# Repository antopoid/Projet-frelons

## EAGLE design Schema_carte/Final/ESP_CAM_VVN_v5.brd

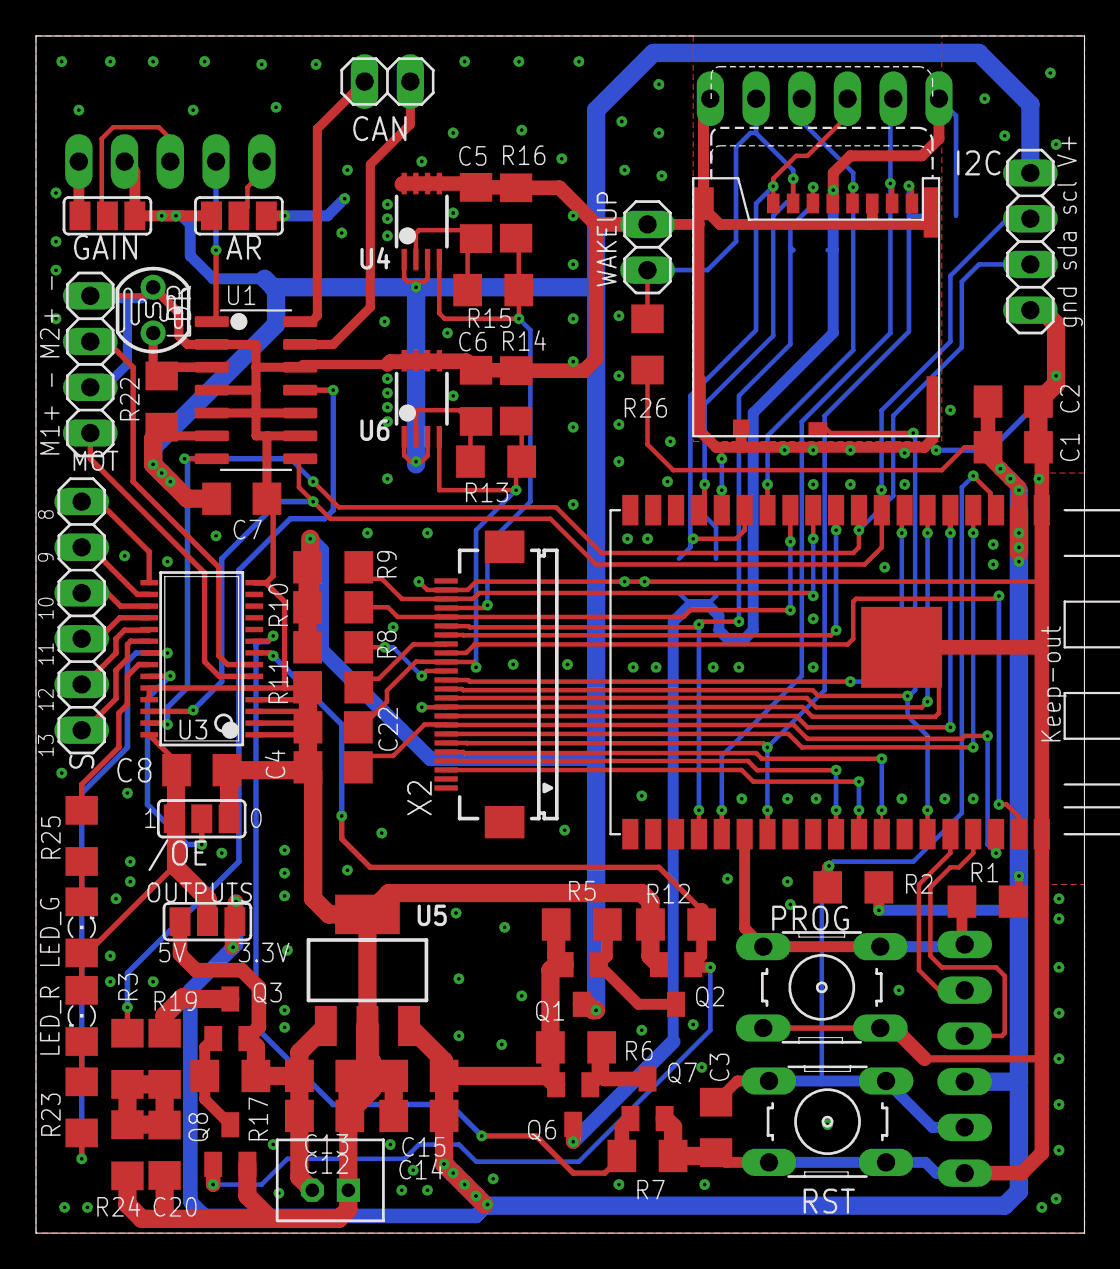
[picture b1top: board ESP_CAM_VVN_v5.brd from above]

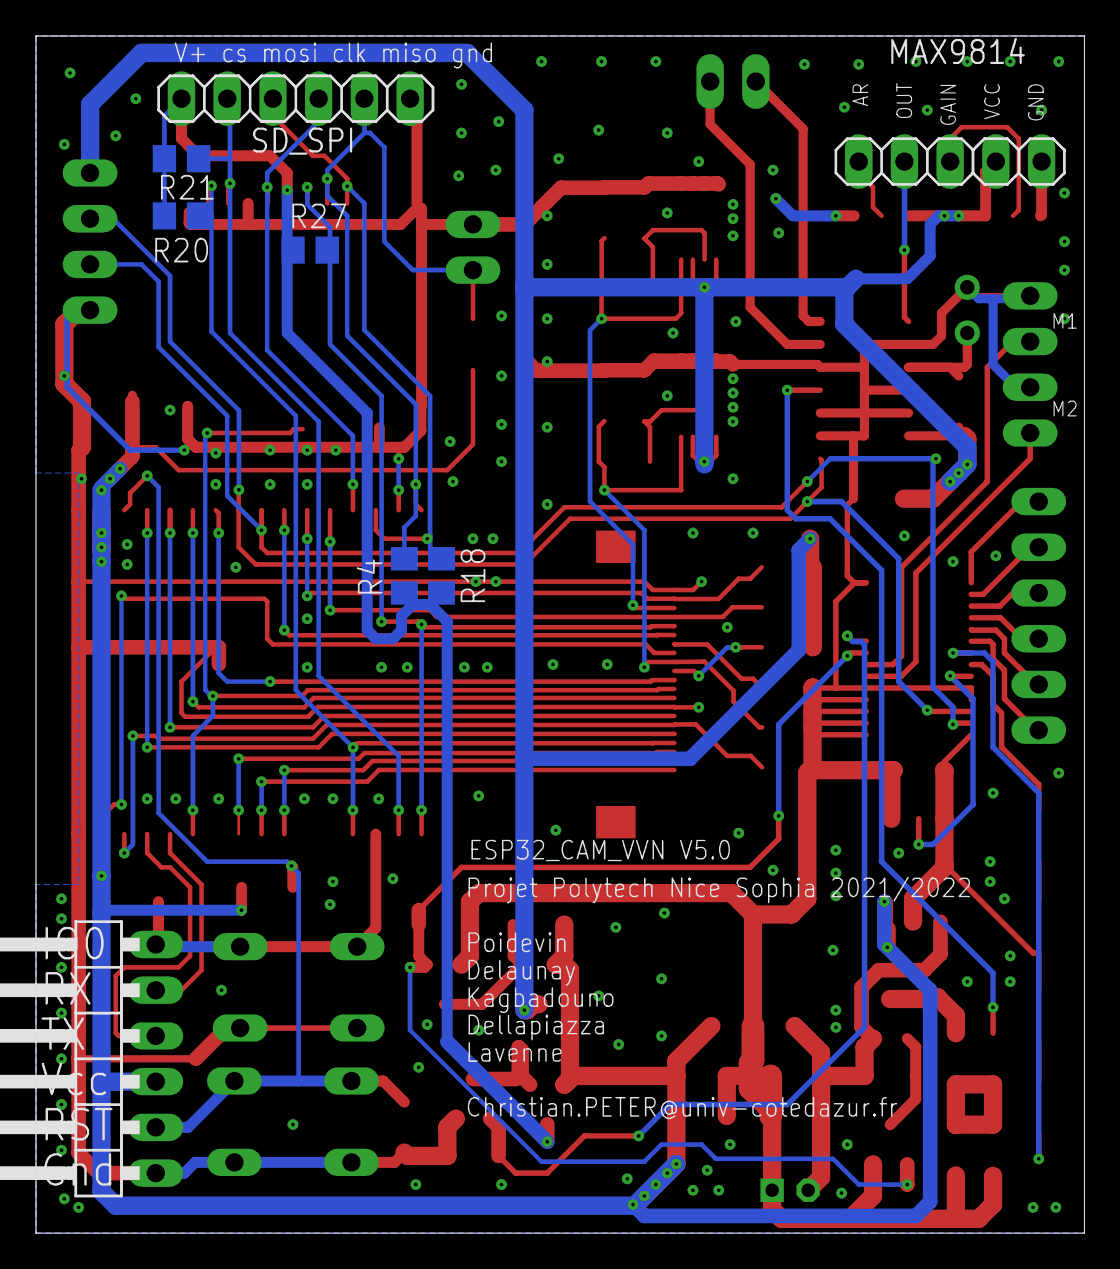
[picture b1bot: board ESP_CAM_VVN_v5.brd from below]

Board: 2 copper layers, 58.2 x 66.5 mm, 73 parts (8 on the bottom side), 64 nets.

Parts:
/OE: SJ_2
AR: SJ_2
C1, C3, C7, C8, C13, C15, C20, C22: 100n; C1206
C2, C12, C14: 10u; C1206
C4: 15p; C1206
C5, C6: 1u; C1206
CAN: 1X02
GAIN: SJ_2
I2C: 1X04
JP6: 1X06/90
LDR: VT93N2; VT900
LED_G: 1206
LED_R: 1206
MAX9814: 1X05
MOT: 1X04
OUTPUTS: SJ_2
PROG: B3F-10XX
Q1, Q3, Q6: SI2305CDS; SOT23
Q2, Q7, Q8: BSS131; SOT23
R1, R13, R26: 100k; R1206
R2, R11, R16, R22, R24: 10k; R1206
R3, R8: 0; R1206
R4, R18, R20, R21, R27: 47k; R0805
R5, R6, R7, R12, R17: 33k; R1206
R9, R10: 4.7K; R1206
R14: 220k; R1206
R15: 12k; R1206
R19: 150k; R1206
R23: 150; R1206
R25: 100; R1206
RST: B3F-10XX
S: 1X06
SD1: MICRO-SD-8; MICROSDMOLEX
SD_SPI: 1X06
U1: MCP3428-E/SL; SOIC127P600X175-14N
U2: ESP32-WROVER-E; ESP32-WROVER
U3: PCA9685PW; TSSOP28
U4, U6: MIC5239-ADJMM; MSOP08
U5: MIC5239S; SOT223
WAKEUP: 1X02
X1: B2B-PH-K-S
X2: FH12-24S-0.5SH

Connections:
5V_MES: R3.1, U1.11
+5V: C12.1, C13.1, OUTPUTS.1, Q3.2, R17.2, U5.1, X1.2
+5V/1: Q3.3, R19.1
AR: AR.2, MAX9814.1
CA_D0_SD_D1: R20.2, SD1.P$1, U2.IO4, X2.6
CA_D1: U2.IO5, X2.4
CA_D2: U2.IO18, X2.3
CA_D3: U2.IO19, X2.5
CA_D4: U2.SENSOR_VP, X2.7
CA_D5: U2.SENSOR_VN, X2.9
CA_D6: U2.IO34, X2.11
CA_D7: U2.IO35, X2.13
CA_HREF: U2.IO23, X2.16
CA_PCLK: C4.2, U2.IO22, X2.8
CA_PWDN: R11.2, X2.17
CA_PWDN_SD_CLK: SD1.P$4, SD_SPI.4, U2.IO14
CA_RST_SD_CMD: R27.2, SD1.P$6, U2.IO15, X2.19
CA_SIO_C: R10.2, U2.IO27, X2.20
CA_SIO_D: R9.2, U2.IO26, X2.22
CA_VSYNC: U2.IO25, X2.18
CA_XCLK_SD_DET: SD1.P$14, U2.IO21, X2.12
GAIN: GAIN.2, MAX9814.3
GND: /OE.1, AR.3, C1.2, C2.2, C3.2, C4.1, C5.2, C6.2, C7.2, C8.2, C12.2, C13.2, C14.2, C15.2, C20.2, C22.2, GAIN.1, I2C.4, JP6.1, LDR.1, MAX9814.5, MOT.2, MOT.4, PROG.3, PROG.4, Q2.2, Q7.2, Q8.2, R7.2, R11.1, R12.2, R14.1, R16.1, R24.2, RST.3, RST.4, SD1.P$3, SD1.P$9, SD1.P$10, SD1.P$11, SD1.P$12, SD1.P$13, SD_SPI.6, U1.2, U1.4, U1.5, U1.9, U1.10, U1.12, U2.GND, U2.GND1, U2.GND2, U2.GND3, U3.1, U3.2, U3.3, U3.4, U3.5, U3.14, U3.24, U3.25, U4.5, U4.6, U4.7, U4.8, U5.2, U5.4, U6.5, U6.6, U6.7, U6.8, WAKEUP.1, X1.1, X2.10, X2.23
IO0: JP6.6, PROG.1, PROG.2, R1.2, U2.IO0
LDR: LDR.2, R22.2, U1.3
LED_G: R25.1, U3.22
LED_R: R23.1, U3.21
M1: MOT.1, U3.6
M2: MOT.3, U3.7
unnamed: Q1.1, Q2.3, R5.1
unnamed: MAX9814.2, U1.1
unnamed: C20.1, R3.2, R19.2, R24.1
unnamed: /OE.3, C8.1, LED_G.A, LED_R.A, OUTPUTS.2, U3.28
unnamed: CAN.2, U1.13
unnamed: Q6.1, Q7.3, R6.1
unnamed: LED_R.C, R23.2
unnamed: LED_G.C, R25.2
unnamed: Q3.1, Q8.3, R17.1
unnamed: R8.2, X2.14
unnamed: CAN.1, U1.14
unnamed: S.1, U3.15
unnamed: S.2, U3.16
unnamed: S.3, U3.17
unnamed: S.4, U3.18
unnamed: S.5, U3.19
unnamed: S.6, U3.20
unnamed: R13.1, R14.2, U6.2
unnamed: R15.1, R16.2, U4.2
OE: /OE.2, U3.23
POWER: Q2.1, Q8.1, R12.1, U3.8
POWER_SD: Q7.1, R7.1, U3.9
RST: C3.1, JP6.2, R2.1, RST.1, RST.2, U2.EN
RX: JP6.5, U2.RXD0
SCL: I2C.2, U1.8, U2.IO32, U3.26
SDA: I2C.3, U1.7, U2.IO33, U3.27
SD_D0: R21.2, SD1.P$2, SD_SPI.2, U2.IO2
SD_D2: R18.2, SD1.P$8, SD_SPI.3, U2.IO12
SD_D3: R4.2, R26.2, SD1.P$7, SD_SPI.5, U2.IO13, WAKEUP.2
TX: JP6.4, U2.TXD0
V1_2.7V: C5.1, R15.2, U4.4, X2.21
V2_1.8V: C6.1, C22.1, R13.2, U6.4, X2.15
V+: AR.1, C7.1, GAIN.3, I2C.1, MAX9814.4, Q1.3, R8.1, R9.1, R10.1, R22.1, U1.6, U4.1, U4.3, U6.1, U6.3
V+_SD: Q6.3, R4.1, R18.1, R20.1, R21.1, R27.1, SD1.P$5, SD_SPI.1
VCC: C1.1, C2.1, C14.1, C15.1, JP6.3, OUTPUTS.3, Q1.2, Q6.2, R1.1, R2.2, R5.2, R6.2, R26.1, U2.VDD33, U5.3

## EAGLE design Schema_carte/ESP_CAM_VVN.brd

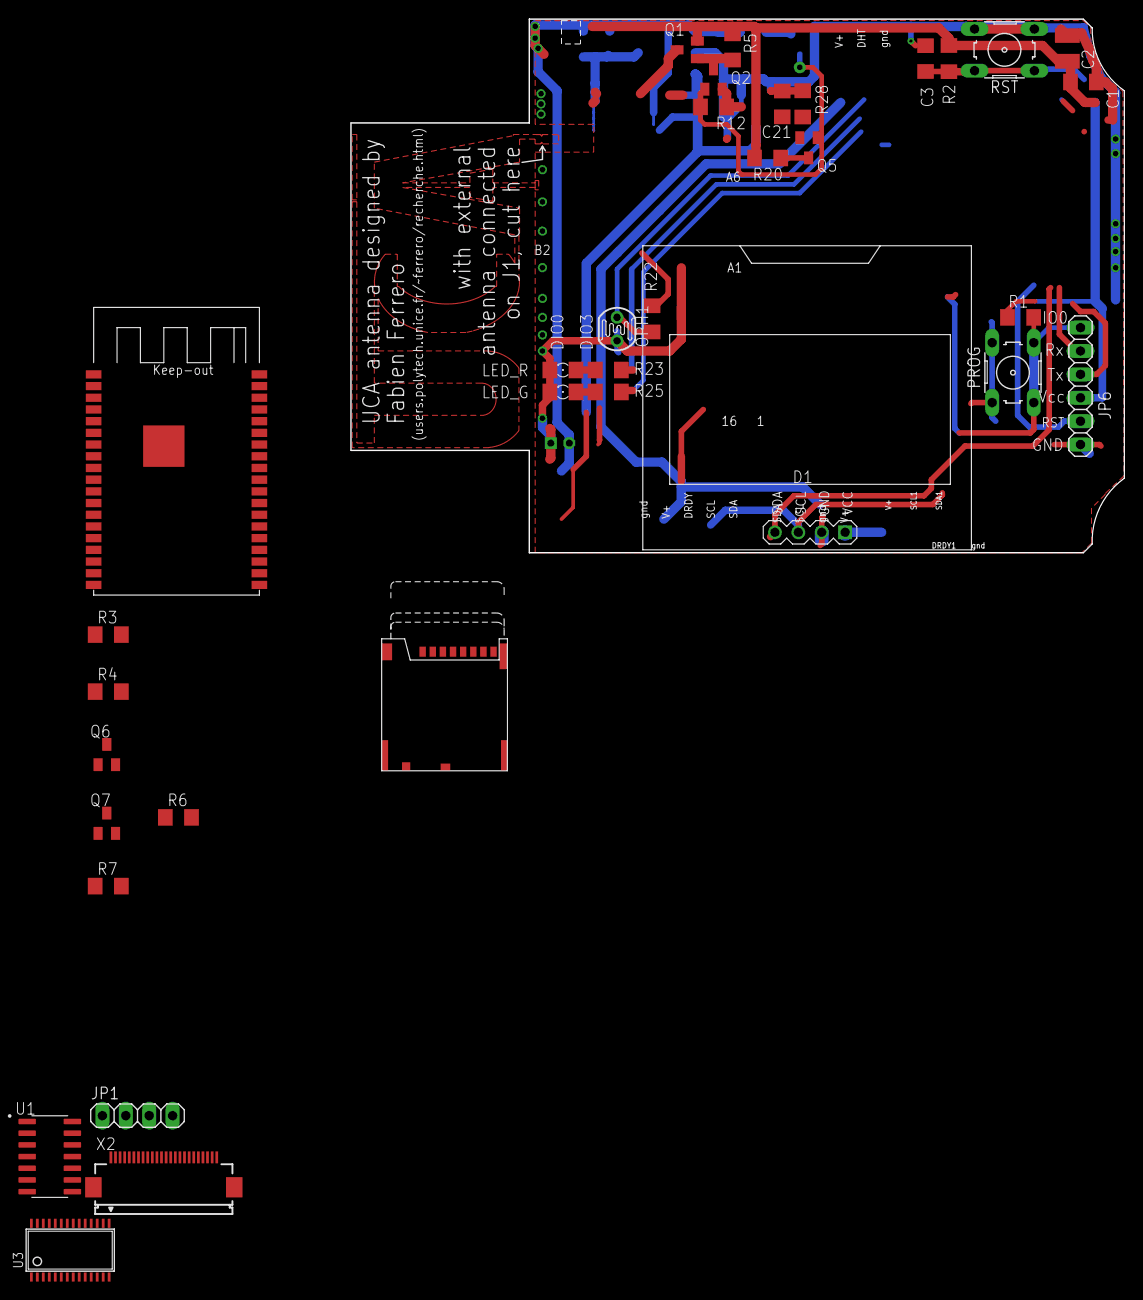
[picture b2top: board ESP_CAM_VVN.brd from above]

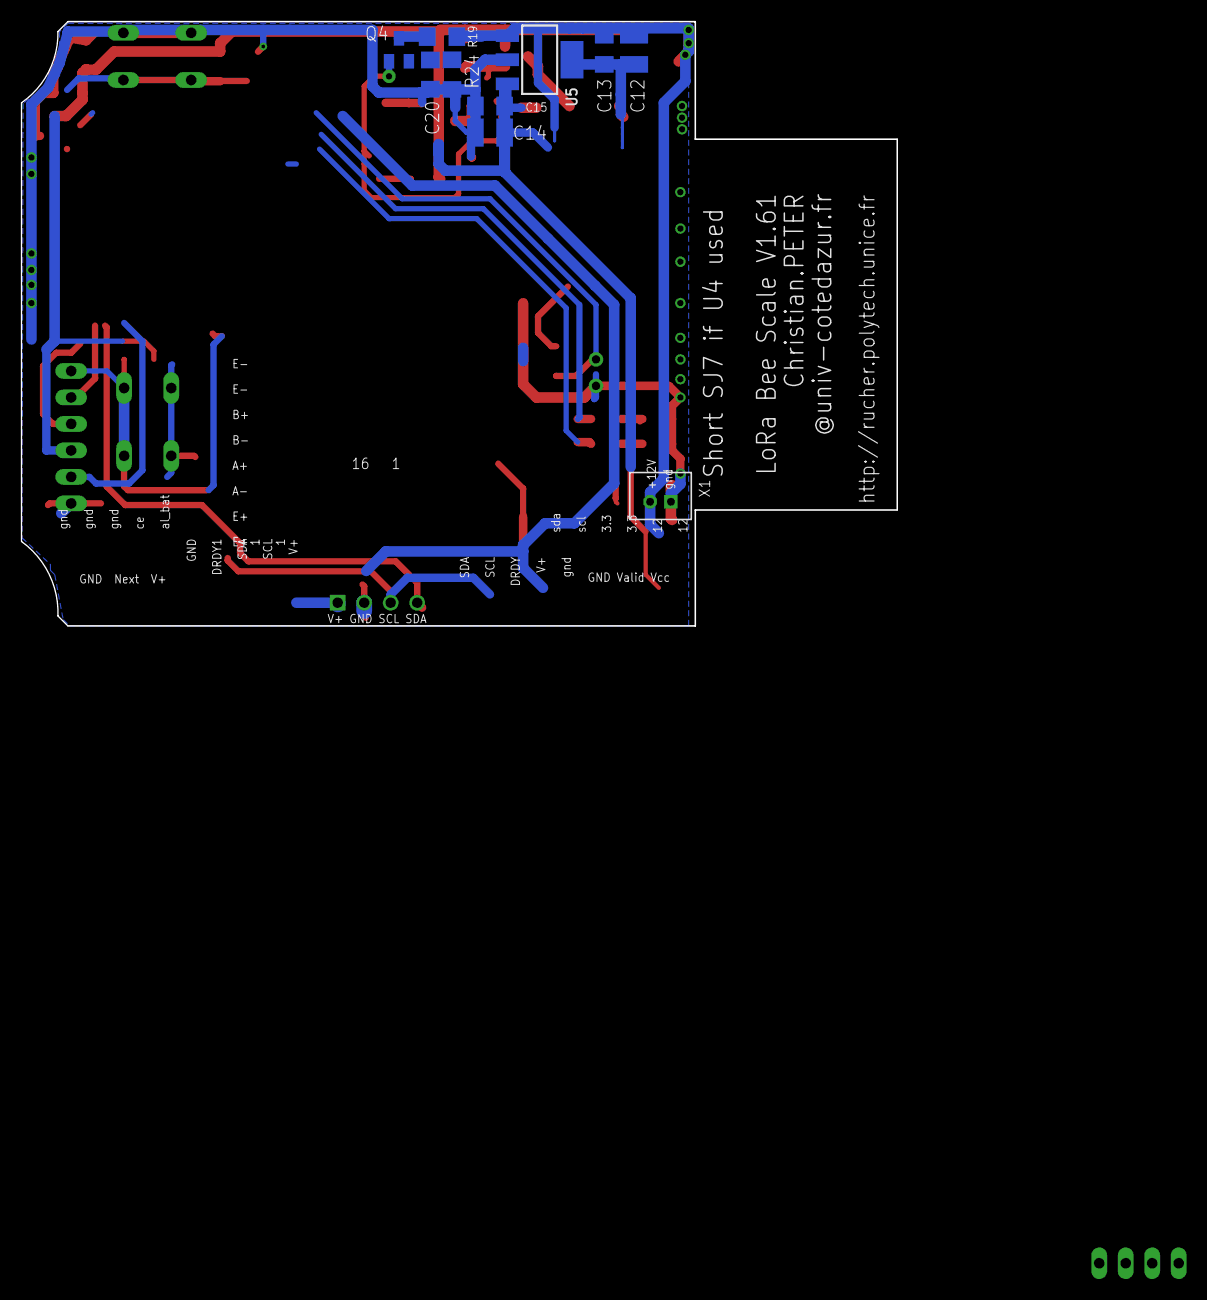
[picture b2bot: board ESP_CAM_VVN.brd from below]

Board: 2 copper layers, 84.0 x 57.9 mm, 45 parts (10 on the bottom side), 28 nets.

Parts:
C1, C3, C13, C15, C20, C21: 100n; C1206
C2, C12, C14: 10u; C1210
D1: DISPLAY-OLED-128X64-I2C1.3_BIS; DISPLAY-OLED-128X64-1.3-I2C_BIS
JP1: 1X04
JP6: 1X06
LED_G: 1206
LED_R: 1206
OPH1: VT93N2; VT900
PROG: B3F-10XX
Q1, Q6: SI2305CDS; SOT23
Q2, Q7: BSS131; SOT23
Q4, Q5: BSS138; SOT23
R1: 100k; R1206
R2, R22, R24, R28: 10k; R1206
R3, R4: 0; R1206
R5, R6, R7, R12: 33k; R1206
R19: 150k; R1206
R20: 27k; R1206
R23: 150; R1206
R25: 100; R1206
RST: B3F-10XX
SD1: MICRO-SD-8; MICROSDMOLEX
U1: MCP3428-E/SL; SOIC127P600X175-14N
U2: ESP32-WROVER-E; ESP32-WROVER
U3: PCA9685PW; TSSOP28
U5: MIC5239S; SOT223
X1: B2B-PH-K-S
X2: FH12-24S-0.5SH

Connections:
+12V: C12.1, C13.1, R19.1, U5.1, X1.2
CA_D0_SD_D1: SD1.P$8, U2.IO4
CA_XCLK_SD_DET: SD1.P$14, U2.IO21
GND: C1.2, C2.2, C3.2, C12.2, C13.2, C14.2, C15.2, C20.2, C21.2, D1.2, JP1.4, JP6.1, LED_G.C, LED_R.C, OPH1.1, PROG.3, PROG.4, Q2.2, Q7.2, R7.2, R12.2, R24.2, R28.2, RST.3, RST.4, SD1.P$6, SD1.P$9, SD1.P$10, SD1.P$11, SD1.P$12, SD1.P$13, U2.GND, U2.GND1, U2.GND2, U2.GND3, U3.14, U5.2, U5.4, X1.1
IO0: JP6.6, PROG.1, PROG.2, R1.2
LDR: OPH1.2, R22.2
unnamed: Q1.1, Q2.3, R5.1
unnamed: Q4.3, R19.2
unnamed: C20.1, Q4.2, R3.2, R24.1
unnamed: C21.1, Q5.2, R4.2, R28.1
unnamed: Q5.3, R20.1
unnamed: Q6.1, Q7.3, R6.1
unnamed: LED_R.A, R23.2
unnamed: LED_G.A, R25.2
POWER: Q2.1, Q4.1, Q5.1, R12.1
POWER_SD: Q7.1, R7.1
RST: C3.1, JP6.2, R2.1, RST.1, RST.2, U2.EN
RX: JP6.5, U2.RXD0
SCL: D1.3, JP1.2, U1.8, U2.IO32
SDA: D1.4, JP1.3, U1.7, U2.IO33, U3.27
SD_CLK: SD1.P$5, U2.IO14
SD_D0: SD1.P$7, U2.IO2
SD_D2: SD1.P$1, U2.IO12
SD_D3: SD1.P$2, U2.IO13
TX: JP6.4, U2.TXD0
V+: D1.1, JP1.1, Q1.3, R22.1, U1.6, U3.28
V+_SD: Q6.3, SD1.P$4
VCC: C1.1, C2.1, C14.1, C15.1, JP6.3, Q1.2, Q6.2, R1.1, R2.2, R5.2, R6.2, R20.2, U2.VDD33, U5.3

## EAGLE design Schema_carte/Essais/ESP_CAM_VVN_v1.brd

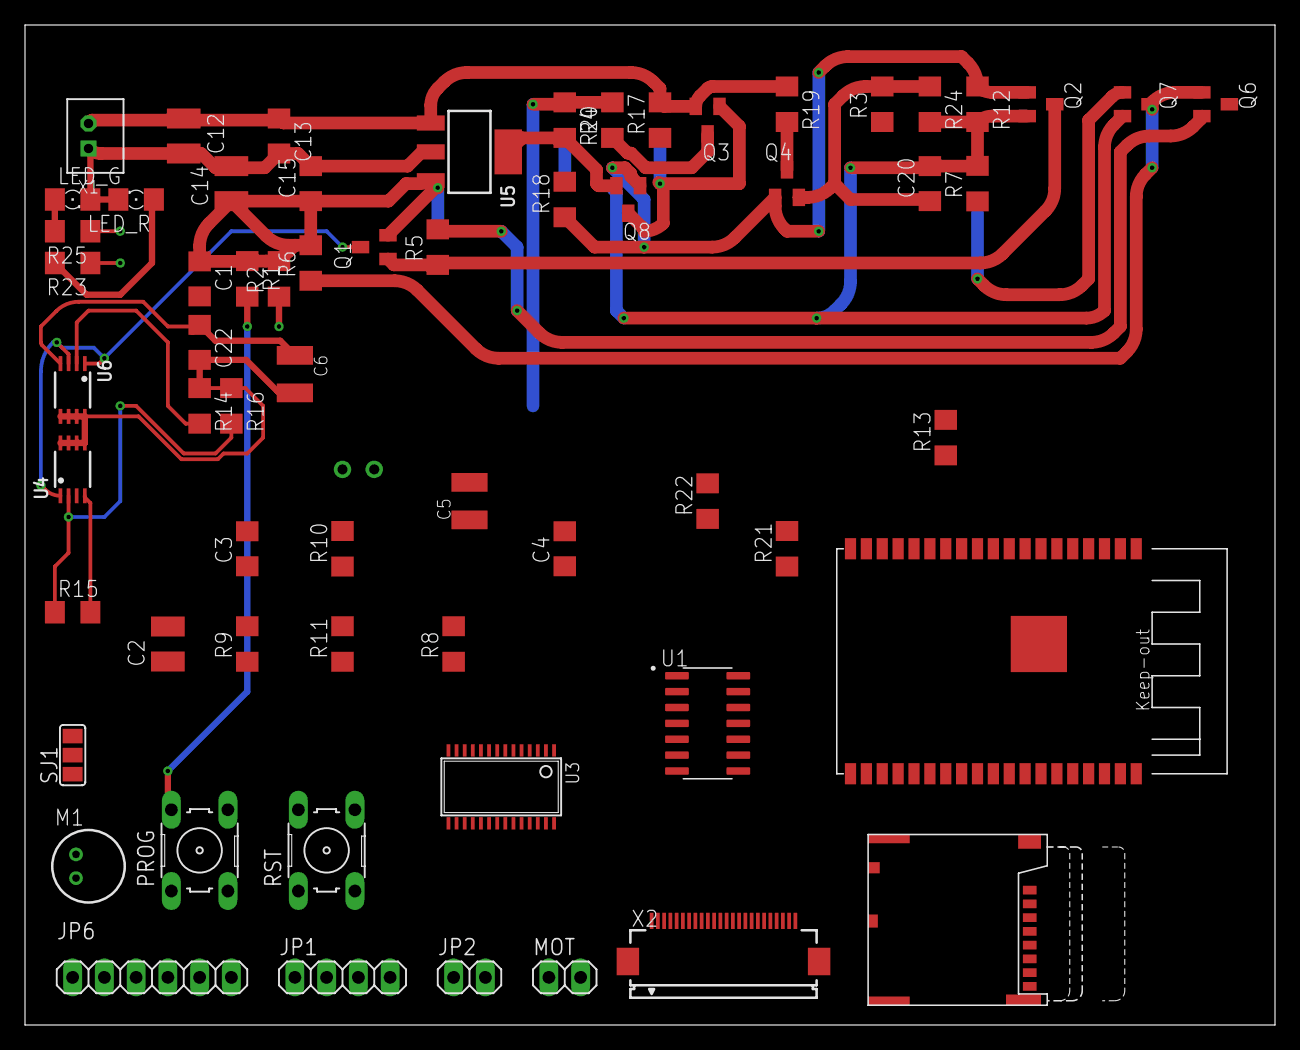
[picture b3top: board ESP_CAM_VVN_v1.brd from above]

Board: 2 copper layers, 100.0 x 80.0 mm, 64 parts (1 on the bottom side), 56 nets.

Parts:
C1, C3, C13, C15, C20, C22: 100n; C1206
C2, C12, C14: 10u; C1210
C4: 15p; C1206
C5, C6: 1u; C1210K
JP1: 1X04
JP2: 1X02
JP6: 1X06
LED_G: 1206
LED_R: 1206
M1: ELECTRET_MICROPHON-WM-62PC/62PK; WM-62PC/62PK
MOT: 1X02
OPH1: VT93N2; VT900
PROG: B3F-10XX
Q1, Q3, Q6: SI2305CDS; SOT23
Q2, Q7, Q8: BSS131; SOT23
Q4: BSS138; SOT23
R1, R13: 100k; R1206
R2, R11, R16, R21, R22, R24: 10k; R1206
R3, R8: 0; R1206
R4, R5, R6, R7, R12, R17, R18, R20: 33k; R1206
R9, R10: 4.7K; R1206
R14: 220k; R1206
R15: 12k; R1206
R19: 150k; R1206
R23: 150; R1206
R25: 100; R1206
RST: B3F-10XX
SD1: MICRO-SD-8; MICROSDMOLEX
SJ1: SJ_2
U1: MCP3428-E/SL; SOIC127P600X175-14N
U2: ESP32-WROVER-E; ESP32-WROVER
U3: PCA9685PW; TSSOP28
U4, U6: MIC5239-ADJMM; MSOP08
U5: MIC5239S; SOT223
X1: B2B-PH-K-S
X2: FH12-24S-0.5SH

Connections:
5V_MES: R4.2, R20.1, U1.11
+5V: C12.1, C13.1, Q3.2, R17.2, R19.1, U5.1, X1.2
+5V/1: Q3.3, R4.1, SJ1.1
CA_D0_SD_D1: SD1.P$8, U2.IO4, X2.19
CA_D1: U2.IO5, X2.21
CA_D2: U2.IO18, X2.22
CA_D3: U2.IO19, X2.20
CA_D4: U2.SENSOR_VP, X2.18
CA_D5: U2.SENSOR_VN, X2.16
CA_D6: U2.IO34, X2.14
CA_D7: U2.IO35, X2.12
CA_HREF: U2.IO23, X2.9
CA_PCLK: C4.2, U2.IO22, X2.17
CA_PWDN: R11.2, X2.8
CA_RST_SD_CMD: SD1.P$3, U2.IO15, X2.6
CA_SIO_C: R10.2, U2.IO27, X2.5
CA_SIO_D: R9.2, U2.IO26, X2.3
CA_VSYNC: U2.IO25, X2.7
CA_XCLK_SD_DET: SD1.P$14, U2.IO21, X2.13
GND: C1.2, C2.2, C3.2, C4.1, C5.2, C6.2, C12.2, C13.2, C14.2, C15.2, C20.2, C22.2, JP1.4, JP6.1, LED_G.C, LED_R.C, M1.1, OPH1.1, PROG.3, PROG.4, Q2.2, Q7.2, Q8.2, R7.2, R11.1, R12.2, R14.1, R16.1, R18.2, R20.2, R24.2, RST.3, RST.4, SD1.P$6, SD1.P$9, SD1.P$10, SD1.P$11, SD1.P$12, SD1.P$13, U1.2, U1.4, U1.12, U2.GND, U2.GND1, U2.GND2, U2.GND3, U3.14, U4.5, U4.6, U4.7, U4.8, U5.2, U5.4, U6.5, U6.6, U6.7, U6.8, X1.1, X2.2, X2.15
IO0: JP6.6, PROG.1, PROG.2, R1.2
LDR: OPH1.2, R22.2, U1.3
LED_G: R25.1, U3.22
LED_R: R23.1, U3.21
unnamed: Q1.1, Q2.3, R5.1
unnamed: Q4.3, R19.2
unnamed: C20.1, Q4.2, R3.2, R24.1
unnamed: SJ1.2, U3.28
unnamed: JP2.2, U1.13
unnamed: Q6.1, Q7.3, R6.1
unnamed: LED_R.A, R23.2
unnamed: LED_G.A, R25.2
unnamed: Q3.1, Q8.3, R17.1
unnamed: R8.2, X2.11
unnamed: M1.2, R21.1, U1.1
unnamed: JP2.1, U1.14
unnamed: MOT.1, U3.6
unnamed: MOT.2, U3.7
unnamed: R13.1, R14.2, U6.2
unnamed: R15.1, R16.2, U4.2
POWER: Q2.1, Q4.1, Q8.1, R12.1, R18.1, U3.8
POWER_SD: Q7.1, R7.1, U3.9
RST: C3.1, JP6.2, R2.1, RST.1, RST.2, U2.EN
RX: JP6.5, U2.RXD0
SCL: JP1.2, U1.8, U2.IO32, U3.26
SDA: JP1.3, U1.7, U2.IO33, U3.27
SD_CLK: SD1.P$5, U2.IO14
SD_D0: SD1.P$7, U2.IO2
SD_D2: SD1.P$1, U2.IO12
SD_D3: SD1.P$2, U2.IO13
TX: JP6.4, U2.TXD0
V1_2.7V: C5.1, R15.2, U4.4
V2_1.8V: C6.1, C22.1, R13.2, U6.4, X2.10
V+: JP1.1, Q1.3, R8.1, R9.1, R10.1, R21.2, R22.1, SJ1.3, U1.6, U4.1, U4.3, U6.1, U6.3
V+_SD: Q6.3, SD1.P$4
VCC: C1.1, C2.1, C14.1, C15.1, JP6.3, Q1.2, Q6.2, R1.1, R2.2, R5.2, R6.2, U2.VDD33, U5.3

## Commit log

2021-08-27 antoine - ancien projet
2021-08-27 romain - test
2021-08-27 romain - creation du fichier
2021-08-27 romain - mise a jour fichier roles
2021-08-27 antoine - doc perso
2021-08-27 antoine - change doc from txt to md
2021-08-27 romain - creation fichiers rapports seance
2021-08-28 antoine - ajout doc perso
2021-08-28 antoine - maj
2021-09-12 Romain mise a jour fichier
2021-09-17 Create Arnaud-Delaunay
2021-09-22 Romain creation fichier
2021-09-22 Romain maj du 17-09-21
2021-09-22 romain maj avec photos
2021-09-23 merge
2021-09-23 Auto stash before merge of "master" and "origin/master"
2021-09-23 antoine - maj doc perso
2021-09-23 Gilbert : creation fichier rapport
2021-09-23 antoine - creation dossiers
2021-09-23 antoine - ajout lien google doc
2021-09-23 ntoine - avec readme dossier perso
2021-09-23 antoine - ajout dossier arnaud
2021-09-23 Romain : creation fichier
2021-09-23 Romain : maj
2021-10-01 Rapport 01/10/2021
2021-10-01 kevin création fichier
2021-10-04 Romain maj fichier
2021-10-13 Romain maj
2021-10-22 romain : creation
2021-10-22 romain creation
2021-10-22 gilbert ajout fichier wrover-cam
2021-10-22 gilbert maj
2021-10-22 romain maj schema
2021-10-22 romain ajout fichier
2021-11-12 gilbert
2021-11-19 romain
2021-12-10 antoine arduino test camera
2022-02-03 antoine - mise a jour rapport sceances
2022-02-06 Update Rapport
2022-02-07 Rapport des seances du semestre par Gilbert Kagbadouno
2022-02-10 antoine - mise a jour rapports sceances
2022-02-10 antoine - test mcp3428 LDR
2022-02-10 Update Rapport Arnaud 10/02/2022
2022-02-10 Mis a jour fait par Gilbert Kagbadouno
2022-02-11 antoine - ajout librairies
2022-02-11 Mis a jour code esp32 cam
2022-02-12 Rapport Arnaud
2022-03-04 antoine - add sd card arduino
2022-03-04 Mis à jour de la dernière séance
2022-03-04 Mis à jour rapport
2022-03-06 antoine - rapport de sceances mis a jour
2022-03-29 Romain ajout dossier exe
2022-03-29 antoine MAj arduino MCP3428
2022-03-29 antoine ajout exec MCP3428
2022-04-03 Mis à jour des rapports de séances
2022-04-03 antoine maj rapport de sceance
2022-05-19 antoine - update fichier peter

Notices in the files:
parts and their libraries:
diy-modules1.8-perso: Released under the Creative Commons Attribution 4.0 International License: http://creativecommons.org/licenses/by/4.0
micrel: Copyright (C) 2008, Bob Starr
